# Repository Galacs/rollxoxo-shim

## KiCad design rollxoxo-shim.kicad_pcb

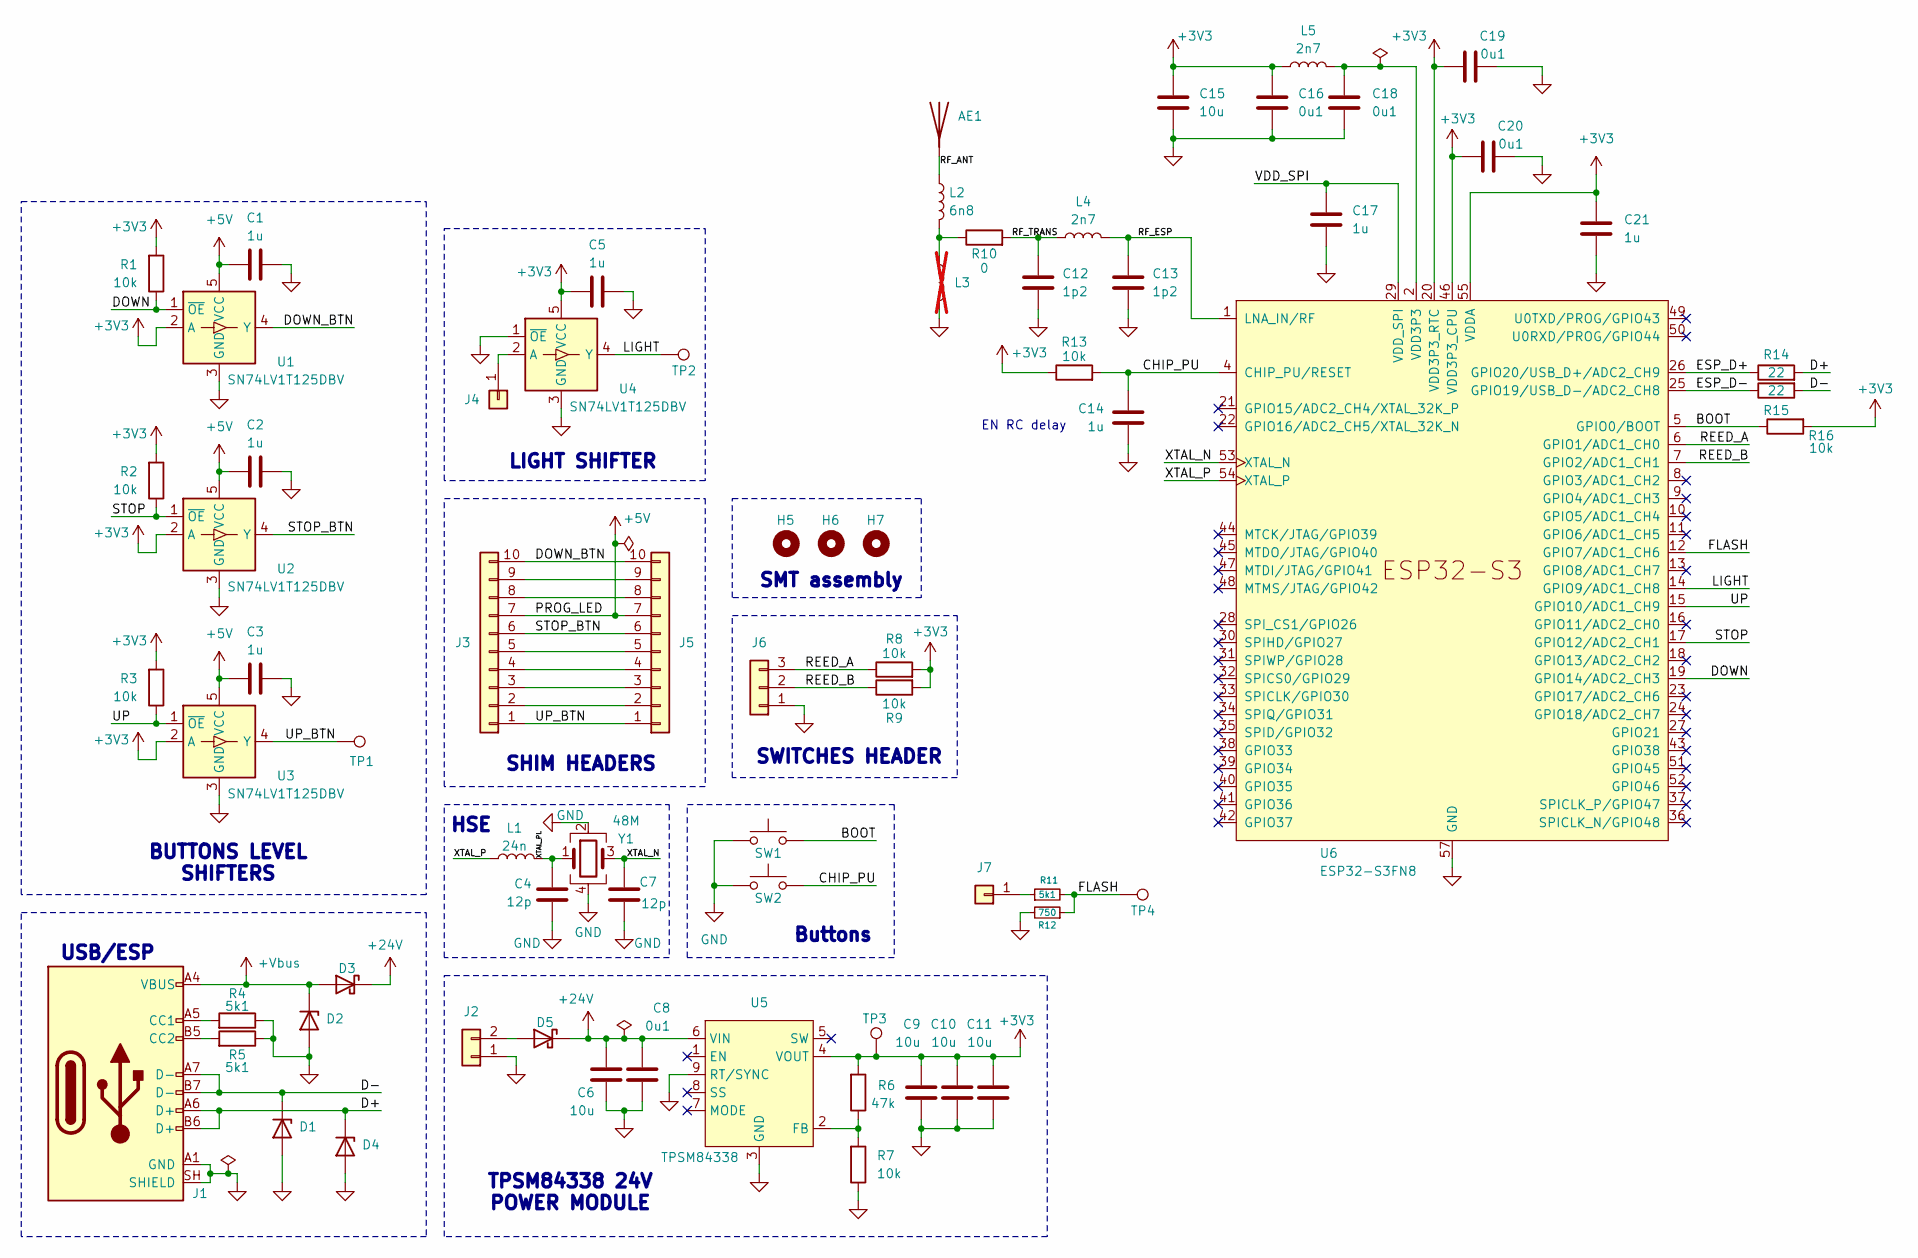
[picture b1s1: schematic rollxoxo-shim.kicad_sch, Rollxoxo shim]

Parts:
AE1: Antenna; Johanson_2450AT18x100; Manufacturer Part Number RFANT3216120A5T; JLCPCB Part # C127629
C1, C2, C3, C5, C14, C17, C21: 1u; C_0402_1005Metric; Manufacturer Part Number CL05A105KA5NQNC; JLCPCB Part # C52923
C4, C7: 12p; C_0402_1005Metric; Manufacturer Part Number 0402CG120J500NT; JLCPCB Part # C1547
C6, C9, C10, C11: 10u; C_0805_2012Metric; Manufacturer Part Number GRM21BR61H106KE43L; JLCPCB Part # C440198
C8, C16, C18, C19, C20: 0u1; C_0402_1005Metric; Manufacturer Part Number CL05B104KB54PNC; JLCPCB Part # C307331
C12, C13: 1p2; C_0402_1005Metric; Manufacturer Part Number GJM1555C1H1R2WB01D; JLCPCB Part # C76899
C15: 10u; C_0402_1005Metric; Manufacturer Part Number CL05A106MQ5NUNC; JLCPCB Part # C15525
D1, D2, D4: H5VU10U; Diode_DFN1006; Manufacturer Part Number H5VU10U; JLCPCB Part # C22395519
D3, D5: D_Schottky; D_SMA; Manufacturer Part Number SS54; JLCPCB Part # C22452
H5, H6, H7: MountingHole; ToolingHole_1.152mm
J1: USB_C_Receptacle_USB2.0_14P; USB_C_Receptacle_HRO_TYPE-C-31-M-12; Manufacturer Part Number TYPE-C16PIN; JLCPCB Part # C393939
J2: Conn_01x02; JST_XH_B2B-XH-A_1x02_P2.50mm_Vertical
J3: Conn_01x10; PinSocket_1x10_P2.54mm_Horizontal
J4, J7: Conn_01x01; PinHeader_1x01_P2.54mm_Horizontal
J5: Conn_01x10; PinHeader_1x10_P2.54mm_Horizontal
J6: Conn_01x03; JST_XH_S3B-XH-A_1x03_P2.50mm_Horizontal
L1: 24n; L_0402_1005Metric; Manufacturer Part Number LQW15AN24NG00D; JLCPCB Part # C167472
L2: 6n8; L_0402_1005Metric; Manufacturer Part Number LQG15HS6N8J02D; JLCPCB Part # C77110
L3: L; L_0402_1005Metric; not fitted
L4, L5: 2n7; L_0402_1005Metric; Manufacturer Part Number LQG15HS2N7S02D; JLCPCB Part # C77108
R1, R2, R3, R7, R8, R9, R13, R16: 10k; R_0402_1005Metric; Manufacturer Part Number 0402WGF1002TCE; JLCPCB Part # C25744
R4, R5: 5k1; R_0402_1005Metric; Manufacturer Part Number 0402WGF5101TCE; JLCPCB Part # C25905
R6: 47k; R_0402_1005Metric; Manufacturer Part Number 0402WGF4702TCE; JLCPCB Part # C25792
R10: 0; R_0402_1005Metric; Manufacturer Part Number 0402WGF0000TCE; JLCPCB Part # C17168
R11: 5k1; R_0603_1608Metric; Manufacturer Part Number 0603WAF5101T5E; JLCPCB Part # C23186
R12: 750; R_0603_1608Metric; Manufacturer Part Number 0603WAF7500T5E; JLCPCB Part # C23241
R14, R15: 22; R_0402_1005Metric; Manufacturer Part Number 0402WGF220JTCE; JLCPCB Part # C25092
SW1, SW2: SW_Push; SW_SPST_TS-1088-xR020; Manufacturer Part Number TS-1088-AR02016; JLCPCB Part # C720477
TP1, TP2, TP3, TP4: TestPoint; TestPoint_Pad_D1.0mm
U1, U2, U3, U4: SN74LV1T125DBV; SOT-23-5; Manufacturer Part Number SN74LV1T125DBVR; JLCPCB Part # C473338
U5: TPSM84338; Manufacturer Part Number TPSM84338RCJR; JLCPCB Part # C47122151
U6: ESP32-S3FN8; QFN-56-1EP_7x7mm_P0.4mm_EP4x4mm_ThermalVias; Manufacturer Part Number ESP32-S3FH4R2; JLCPCB Part # C3013940
Y1: 48M; Crystal_SMD_2016-4Pin_2.0x1.6mm; Manufacturer Part Number R940000096; JLCPCB Part # C7206306

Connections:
+3V3: C5.1, C9.1, C10.1, C11.1, C15.1, C16.1, C19.1, C20.1, C21.1, L5.1, R1.2, R2.2, R3.2, R6.2, R8.2, R9.2, R13.1, R16.2, TP3.1 (1_1), U1.2 (A), U2.2 (A), U3.2 (A), U4.5 (VCC), U5.4 (VOUT), U6.20 (VDD3P3_RTC), U6.46 (VDD3P3_CPU), U6.55 (VDDA), U6.56 (VDDA)
+5V: C1.1, C2.1, C3.1, J3.7, J5.7, U1.5 (VCC), U2.5 (VCC), U3.5 (VCC)
+24V: C6.1, C8.1, D3.1 (K), D5.1 (K), U5.6 (VIN)
+Vbus: D2.1 (K), D3.2 (A), J1.A4 (VBUS), J1.A9 (VBUS), J1.B4 (VBUS), J1.B9 (VBUS)
/BOOT: R16.1, SW1.2, U6.5 (GPIO0/BOOT)
/CHIP_PU: C14.1, R13.2, SW2.2, U6.4 (CHIP_PU/RESET)
/D+: D4.1 (K), J1.A6 (D+), J1.B6 (D+), R14.2
/D-: D1.1 (K), J1.A7 (D-), J1.B7 (D-), R15.2
/DOWN: R1.1, U1.1 (~OE), U6.19 (GPIO14/ADC2_CH3)
/DOWN_BTN: J3.10, J5.10, U1.4 (Y)
/ESP_D+: R14.1, U6.26 (GPIO20/USB_D+/ADC2_CH9)
/ESP_D-: R15.1, U6.25 (GPIO19/USB_D-/ADC2_CH8)
/FLASH: R11.2, R12.1, TP4.1 (1_1), U6.12 (GPIO7/ADC1_CH6)
/LIGHT: TP2.1 (1_1), U4.4 (Y), U6.14 (GPIO9/ADC1_CH8)
/REED_A: J6.3, R8.1, U6.6 (GPIO1/ADC1_CH0)
/REED_B: J6.2, R9.1, U6.7 (GPIO2/ADC1_CH1)
/RF_ANT: AE1.1 (A_1), L2.1
/RF_ESP: C13.1, L4.2, U6.1 (LNA_IN/RF)
/RF_TRANS: C12.1, L4.1, R10.2
/STOP: R2.1, U2.1 (~OE), U6.17 (GPIO12/ADC2_CH1)
/STOP_BTN: J3.6, J5.6, U2.4 (Y)
/UP: R3.1, U3.1 (~OE), U6.15 (GPIO10/ADC1_CH9)
/UP_BTN: J3.1, J5.1, TP1.1 (1_1), U3.4 (Y)
/VDD_SPI: C17.1, U6.29 (VDD_SPI)
/XTAL_N: C7.1, U6.53 (XTAL_N), Y1.3
/XTAL_P: L1.1, U6.54 (XTAL_P)
/XTAL_PL: C4.2, L1.2, Y1.1
GND: C1.2, C2.2, C3.2, C4.1, C5.2, C6.2, C7.2, C8.2, C9.2, C10.2, C11.2, C12.2, C13.2, C14.2, C15.2, C16.2, C17.2, C18.2, C19.2, C20.2, C21.2, D1.2 (A), D2.2 (A), D4.2 (A), J1.A1 (GND), J1.A12 (GND), J1.B1 (GND), J1.B12 (GND), J1.SH (SHIELD), J2.1, J6.1, L3.2, R4.1, R5.1, R7.1, R12.2, SW1.1, SW2.1, U1.3 (GND), U2.3 (GND), U3.3 (GND), U4.1 (~OE), U4.3 (GND), U5.3 (GND), U5.9 (RT/SYNC), U6.57 (GND), Y1.2, Y1.4
unnamed: D5.2 (A), J2.2
unnamed: J1.A5 (CC1), R4.2
unnamed: J1.B5 (CC2), R5.2
unnamed: J3.2, J5.2
unnamed: J3.3, J5.3
unnamed: J3.4, J5.4
unnamed: J3.5, J5.5
unnamed: J3.8, J5.8
unnamed: J3.9, J5.9
unnamed: J4.1 (Pin_1_1), U4.2 (A)
unnamed: J7.1 (Pin_1_1), R11.1
unnamed: L2.2, L3.1, R10.1
unnamed: R6.1, R7.2, U5.2 (FB)
VDD3P3: C18.1, L5.2, U6.2 (VDD3P3), U6.3 (VDD3P3)

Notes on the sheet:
LIGHT SHIFTER
BUTTONS LEVEL SHIFTERS
SWITCHES HEADER
USB/ESP
SMT assembly
HSE
TPSM84338 24V POWER MODULE
EN RC delay
SHIM HEADERS
Buttons

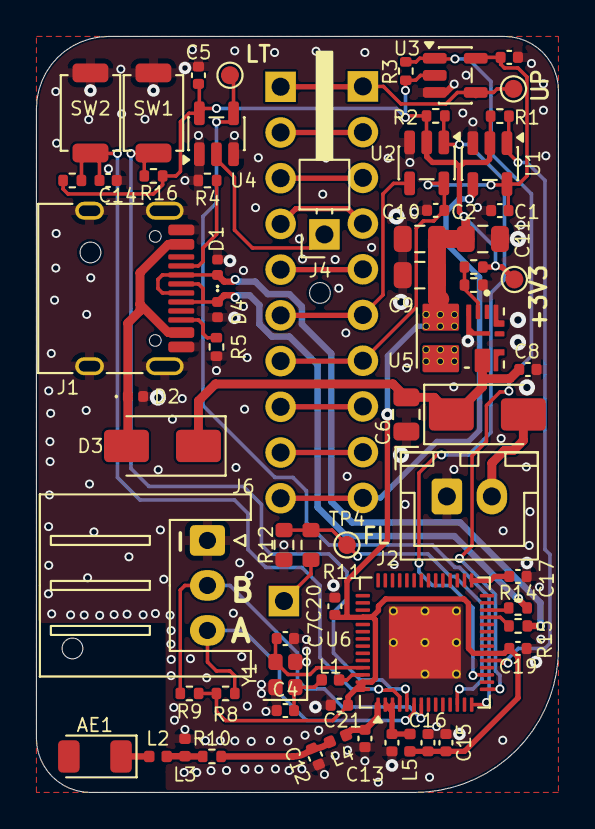
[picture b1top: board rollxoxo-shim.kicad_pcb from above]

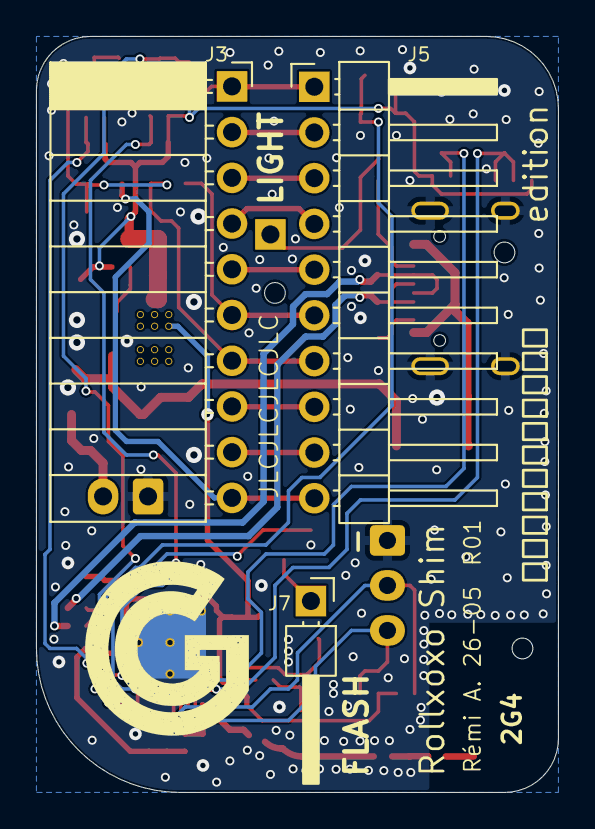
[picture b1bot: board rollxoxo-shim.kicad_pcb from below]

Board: 4 copper layers, 29.0 x 42.0 mm, 71 parts (3 on the bottom side), 42 nets.

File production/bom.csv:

Designator,Footprint,Quantity,Value,LCSC Part #
AE1,Johanson_2450AT18x100,1,Antenna,C127629
"C1, C14, C17, C2, C21, C3, C5",0402,7,1u,C52923
"C10, C11, C6, C9",0805,4,10u,C440198
"C12, C13",0402,2,1p2,C76899
C15,0402,1,10u,C15525
"C16, C18, C19, C20, C8",0402,5,0u1,C307331
"C4, C7",0402,2,12p,C1547
"D1, D2, D4",Diode_DFN1006,3,H5VU10U,C22395519
"D3, D5",D_SMA,2,D_Schottky,C22452
J1,USB_C_Receptacle_HRO_TYPE-C-31-M-12,1,USB_C_Receptacle_USB2.0_14P,C393939
L1,0402,1,24n,C167472
L2,0402,1,6n8,C77110
"L4, L5",0402,2,2n7,C77108
"R1, R13, R16, R2, R3, R7, R8, R9",0402,8,10k,C25744
R10,0402,1,0,C17168
R11,0603,1,5k1,C23186
R12,0603,1,750,C23241
"R14, R15",0402,2,22,C25092
"R4, R5",0402,2,5k1,C25905
R6,0402,1,47k,C25792
"SW1, SW2",SW_SPST_TS-1088-xR020,2,SW_Push,C720477
"U1, U2, U3, U4",SOT-23-5,4,SN74LV1T125DBV,C473338
U5,TPSM84338,1,TPSM84338,C47122151
U6,QFN-56-1EP_7x7mm_P0.4mm_EP4x4mm_ThermalVias,1,ESP32-S3FN8,C3013940
Y1,Crystal_SMD_2016-4Pin_2.0x1.6mm,1,48M,C7206306

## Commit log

2026-06-27 schem: import esp32 and support circuits
2026-06-27 schem: add SN74LV1T125DBV level shifters
2026-06-27 schem: add TPSM84338 24V power module
2026-06-27 schem: add LIGHT level shifter
2026-06-27 schem: reorganize
2026-06-27 schem: add reed switches header
2026-06-27 schem: add flash voltage divider input
2026-06-27 schem: add test points
2026-06-27 schem: connect gpios
2026-06-27 schem: add +5v from shim
2026-06-27 schem: run and fix ERC
2026-06-27 schem: import net classes
2026-06-27 schem: remove uart headers
2026-06-27 schem: assign footprints
2026-06-27 schem: add ordering info to BOM
2026-06-27 schem: add title
2026-06-27 schem: renumber
2026-06-27 pcb: import jlc 4 layer stackup
2026-06-27 pcb: import footprints from schem
2026-06-27 pcb: add missing 3d model
2026-06-27 pcb: initial rough placement
2026-06-27 pcb: add esp32 layout
2026-06-27 pcb: add +3v3 pwr module layout
2026-06-27 pcb: add usb layout
2026-06-27 pcb: add all layout
2026-06-27 pcb: refine layout
2026-06-27 pcb: add board outline
2026-06-27 pcb: add gnd planes
2026-06-27 pcb: add rf layout
2026-06-27 pcb: add gnd vias
2026-06-27 pcb: add drill/place origin
2026-06-27 pcb: reorganize programmable gpios
2026-06-27 pcb: add rf routing
2026-06-27 pcb: add usb routing
2026-06-27 pcb: add misc routing
2026-06-27 pcb: add power module routing
2026-06-27 pcb: add +3v3 pwr routing
2026-06-27 pcb: add through routing
2026-06-27 pcb: add +5v routing
2026-06-27 pcb: route gpios
2026-06-27 pcb: route missing
2026-06-27 pcb: add stiching vias
2026-06-27 pcb: run and fix DRC
2026-06-27 pcb: remove unused internal pads
2026-06-27 pcb(silk): clean reference designators
2026-06-27 pcb(silk): add user txt
2026-06-27 pcb: add title
2026-06-27 generate production files
2026-06-30 schem/pcb: add tooling holes
2026-06-30 regenerate production files
